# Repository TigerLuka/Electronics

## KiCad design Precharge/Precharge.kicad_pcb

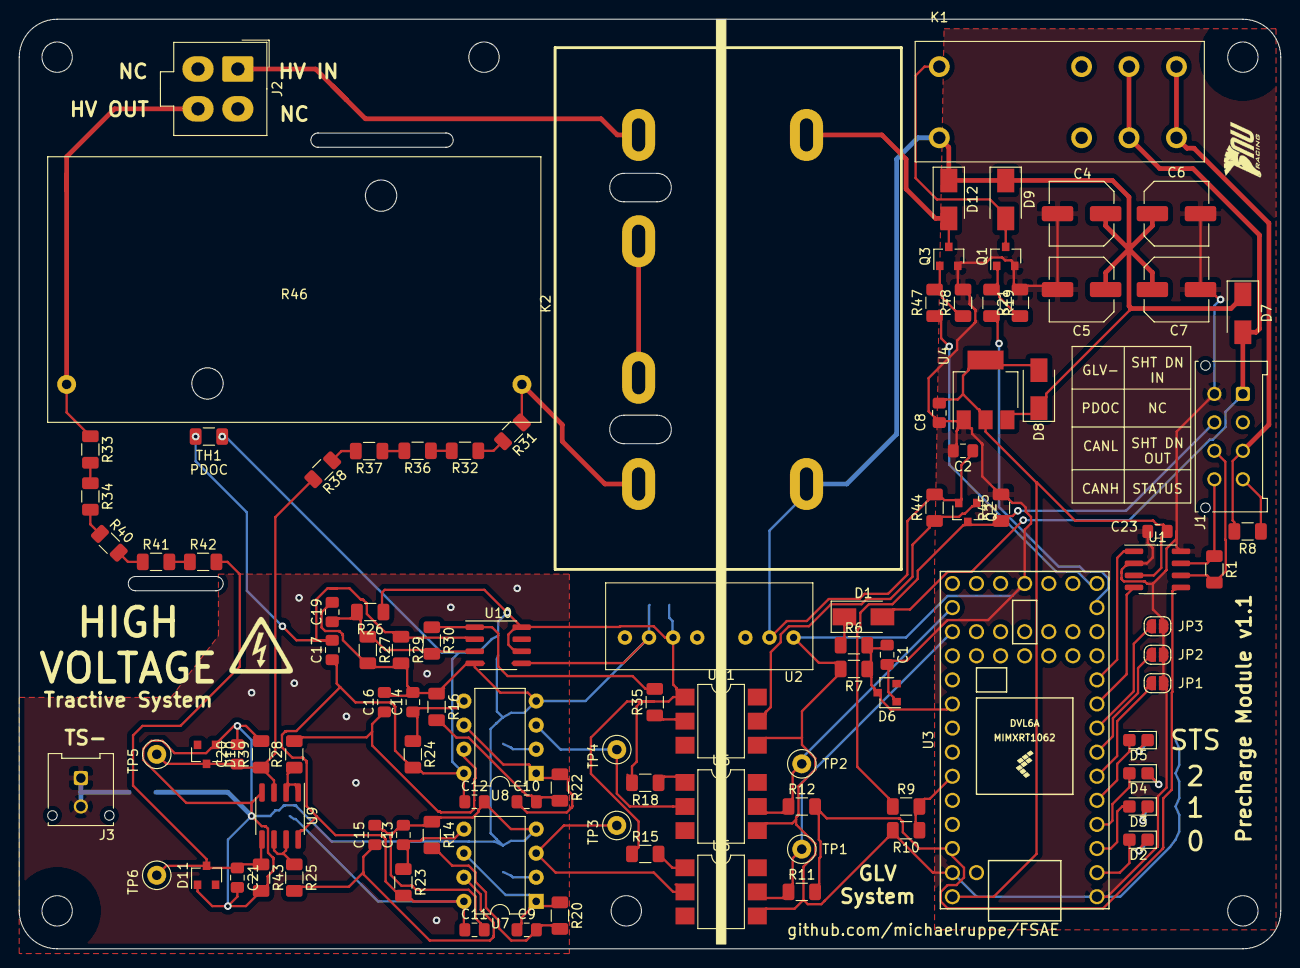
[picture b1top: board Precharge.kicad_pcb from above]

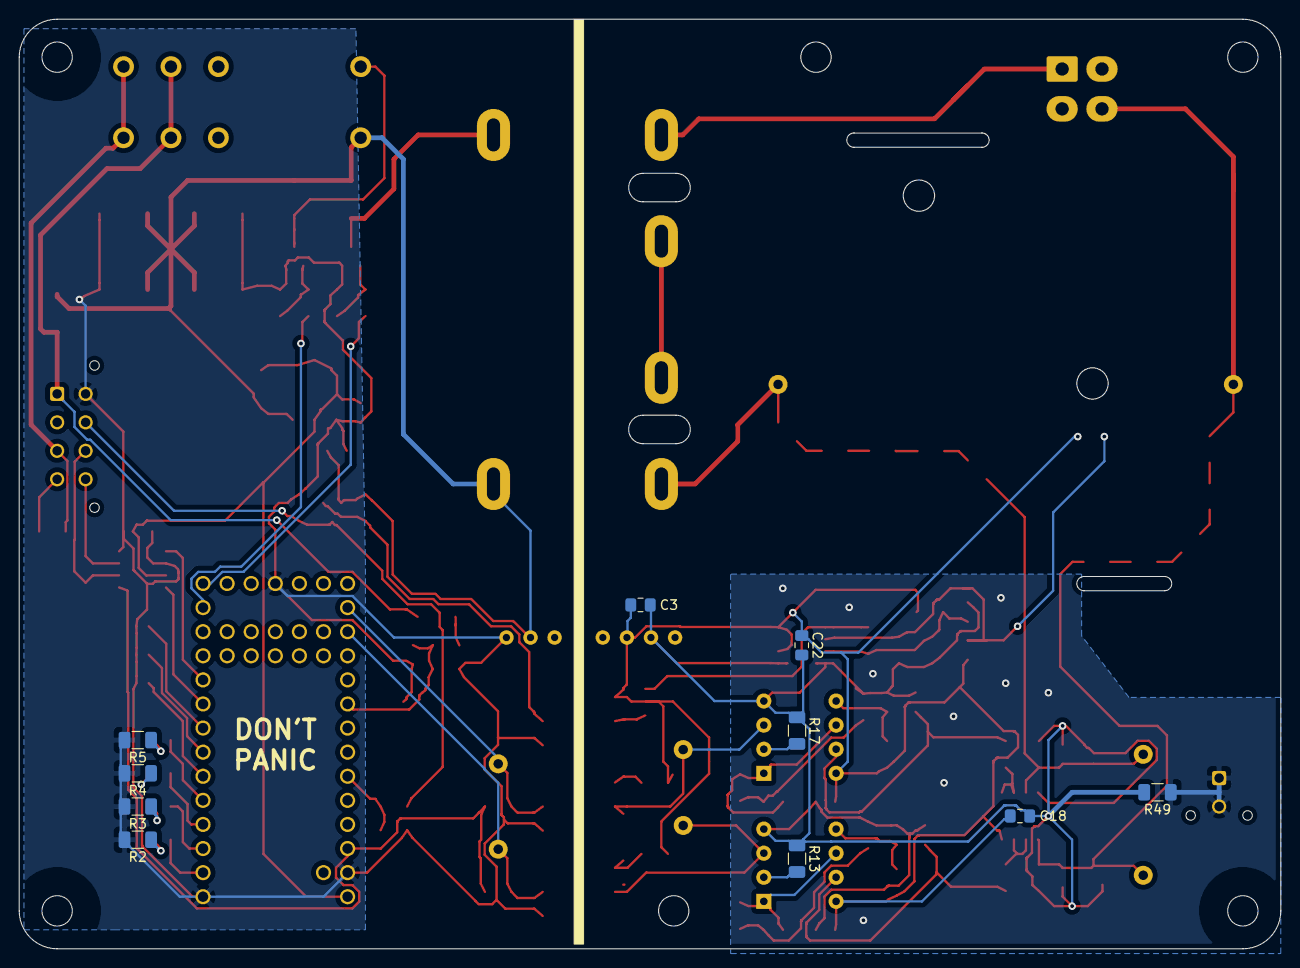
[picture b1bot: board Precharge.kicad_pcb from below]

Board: 2 copper layers, 133.0 x 98.0 mm, 119 parts (10 on the bottom side), 72 nets.

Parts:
C1, C2, C11, C12, C15, C16, C17, C18, C19, C20, C21, C22, C23: 100n; C_0805_2012Metric_Pad1.15x1.40mm_HandSolder
C3, C8, C9, C10: 1u; C_0805_2012Metric_Pad1.15x1.40mm_HandSolder
C4, C5, C6, C7: 220u; C_Elec_6.3x5.4
C13, C14: 10n; C_0805_2012Metric_Pad1.15x1.40mm_HandSolder
D1, D7, D8, D9, D12: D; D_SMA
D2, D3, D4, D5: LED; LED_0805_2012Metric_Castellated
D6: BZX84C3V3; D_SOT-23_ANK
D10, D11: BZX84C12; D_SOT-23_ANK
J1: MicroFit; Molex_Micro-Fit_3.0_43045-0812_2x04_P3.00mm_Vertical
J2: Mini-Fit_Jr_5566-04A; Molex-Mini-Fit-Jr-4-pin-P4.2mm-RowP4.2mm
J3: Micro-Fit 43045-0212; Molex_Micro-Fit_3.0_43045-0212_2x01_P3.00mm_Vertical
JP1, JP2, JP3: SolderJumper_2_Open; SolderJumper-2_P1.3mm_Open_RoundedPad1.0x1.5mm
K1: OMRON-G2RL-24; OMRON-G2R-24
K2: G7L-2A-X-L
MT1, MT2, MT3, MT4, MT5, MT6: MountingHole_3.2mm_M3
Q1, Q3: 2N7002; SOT-23
Q2: MMBT3906; SOT-23
R1: 160; R_1206_3216Metric
R2, R3, R4, R5: 200; R_1206_3216Metric
R6, R9: 20k; R_1206_3216Metric
R7, R10, R23, R24: 6k8; R_1206_3216Metric
R8, R21, R26, R27, R29, R44, R45, R48: 10k; R_1206_3216Metric
R11, R12: 1k5; R_1206_3216Metric
R13, R17: 12k; R_1206_3216Metric
R14, R16: 47; R_1206_3216Metric
R15, R18: 560; R_1206_3216Metric
R19, R47: 220; R_1206_3216Metric
R20, R22, R25, R28: 100k; R_1206_3216Metric
R30: 500k; R_1206_3216Metric
R31, R32, R33, R34, R36, R37, R38, R40, R41, R42: 510k; R_1206_3216Metric
R35: 2k2; R_1206_3216Metric
R39, R43: 39k; R_1206_3216Metric
R46: HSA25390RJ; Chassis_Resistor_TE_Connectivity_HSA25
R49: 0; R_1206_3216Metric
TH1: TFPT1206L1002FM; R_1206_3216Metric
TP1, TP2, TP3, TP4, TP5, TP6: TestPoint; TestPoint_Loop_D2.50mm_Drill1.0mm_LowProfile
U1: TJA1051T-3; SOIC-8_3.9x4.9mm_P1.27mm
U2: SPAN02A-12; SPAN02
U3: Teensy4.0; Teensy40
U4: LM1117-5.0; SOT-223-3_TabPin2
U5, U6, U11: 4N35; SMDIP-6_W7.62mm
U7, U8: LM331; DIP-8_W7.62mm
U9: LM2904; SOIC-8_3.9x4.9mm_P1.27mm
U10: LM393; SOIC-8_3.9x4.9mm_P1.27mm

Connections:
+3V3: R11.2, R12.2, U1.5, U3.31
+5V: C8.1, C23.2, D8.2, U1.3, U3.33, U4.2
+12P: C3.2, C11.1, C12.1, C17.1, C18.1, C22.1, R15.1, R18.2, R23.2, R24.2, R26.1, TH1.2, U2.6, U7.8, U8.8, U9.8, U10.6, U10.8, U11.1
+12V: C2.1, C4.1, C5.1, C6.1, C7.1, D7.1, D8.1, D9.1, D12.1, K1.8, K2.0, Q2.2, R44.2, U2.2, U4.3
/CANH: J1.8, R1.1, U1.7
/CANL: J1.7, R1.2, U1.6
/CANRX: U1.4, U3.9
/CANTX: U1.1, U3.10
/CFG0: JP1.1, U3.6
/CFG1: JP2.1, U3.7
/CFG2: JP3.1, U3.8
/Faccu: R12.1, TP2.1, U3.21, U6.5
/FoutAccu: TP4.1, U6.2, U8.3
/FoutTS: TP3.1, U5.2, U7.3
/Fts: R11.1, TP1.1, U3.22, U5.5
/PDOC_OK: J1.6, Q2.3, R9.1, R45.1
/PRECHG: R47.1, U3.14
/PRECH_STS: J1.4, R8.1
/PWR_OK: C1.1, D6.1, R6.2, R7.1, U3.25
/SHTDN_CTRL: R19.2, U3.13
/SHTDN_OUT: J1.3, K1.4, K1.5, R8.2
/TS-: J3.1, J3.2, R49.1
/VinAccu: K2.2, R31.1, R46.1
/VinTS: J2.4, R33.1, R46.2
GLV+: D1.2, D7.2, J1.1, K1.3, K1.6
GLV-: C1.2, C2.2, C4.2, C5.2, C6.2, C7.2, C8.2, C23.1, D6.2, J1.5, JP1.2, JP2.2, JP3.2, Q1.2, Q3.2, R2.2, R3.2, R4.2, R5.2, R7.2, R10.2, R21.2, R45.2, R48.2, U1.2, U1.8, U2.1, U3.1, U3.17, U3.32, U4.1, U5.4, U6.4, U11.4
GNDS: C3.1, C11.2, C12.2, C13.2, C14.2, C15.2, C16.2, C18.2, C19.2, C20.2, C21.2, C22.2, D10.2, D11.2, R13.1, R14.1, R16.1, R17.1, R27.2, R29.2, R39.2, R43.2, R49.2, U2.7, U7.4, U8.4, U9.4, U10.4, U10.5
unnamed: C9.1, R20.1, U7.1, U7.6
unnamed: C9.2, R14.2, R20.2
unnamed: C10.1, R22.1, U8.1, U8.6
unnamed: C10.2, R16.2, R22.2
unnamed: C13.1, R23.1, U7.5
unnamed: C14.1, R24.1, U8.5
unnamed: C15.1, R25.2, U7.7
unnamed: C16.1, R28.2, U8.7
unnamed: C17.2, R29.1, TH1.1, U10.2
unnamed: C19.1, R26.2, R27.1, R30.2, U10.3
unnamed: C20.1, D10.1, R38.2, R39.1, TP5.1, U9.3
unnamed: C21.1, D11.1, R42.2, R43.1, TP6.1, U9.5
unnamed: D1.1, R6.1
unnamed: D2.1, R2.1
unnamed: D2.2, U3.2
unnamed: D3.1, R3.1
unnamed: D3.2, U3.3
unnamed: D4.1, R4.1
unnamed: D4.2, U3.4
unnamed: D5.1, R5.1
unnamed: D5.2, U3.5
unnamed: D9.2, K1.1, Q1.3
unnamed: D12.2, K2.1, Q3.3
unnamed: J2.1, K2.8
unnamed: K2.4, K2.6
unnamed: Q1.1, R19.1, R21.1
unnamed: Q2.1, R44.1, U11.5
unnamed: Q3.1, R47.2, R48.1
unnamed: R9.2, R10.1, U3.28
unnamed: R13.2, U7.2
unnamed: R15.2, U5.1
unnamed: R17.2, U8.2
unnamed: R18.1, U6.1
unnamed: R25.1, U9.6, U9.7
unnamed: R28.1, U9.1, U9.2
unnamed: R30.1, R35.2, U10.1
unnamed: R31.2, R32.1
unnamed: R32.2, R36.1
unnamed: R33.2, R34.1
unnamed: R34.2, R40.1
unnamed: R35.1, U11.2
unnamed: R36.2, R37.1
unnamed: R37.2, R38.1
unnamed: R40.2, R41.1
unnamed: R41.2, R42.1

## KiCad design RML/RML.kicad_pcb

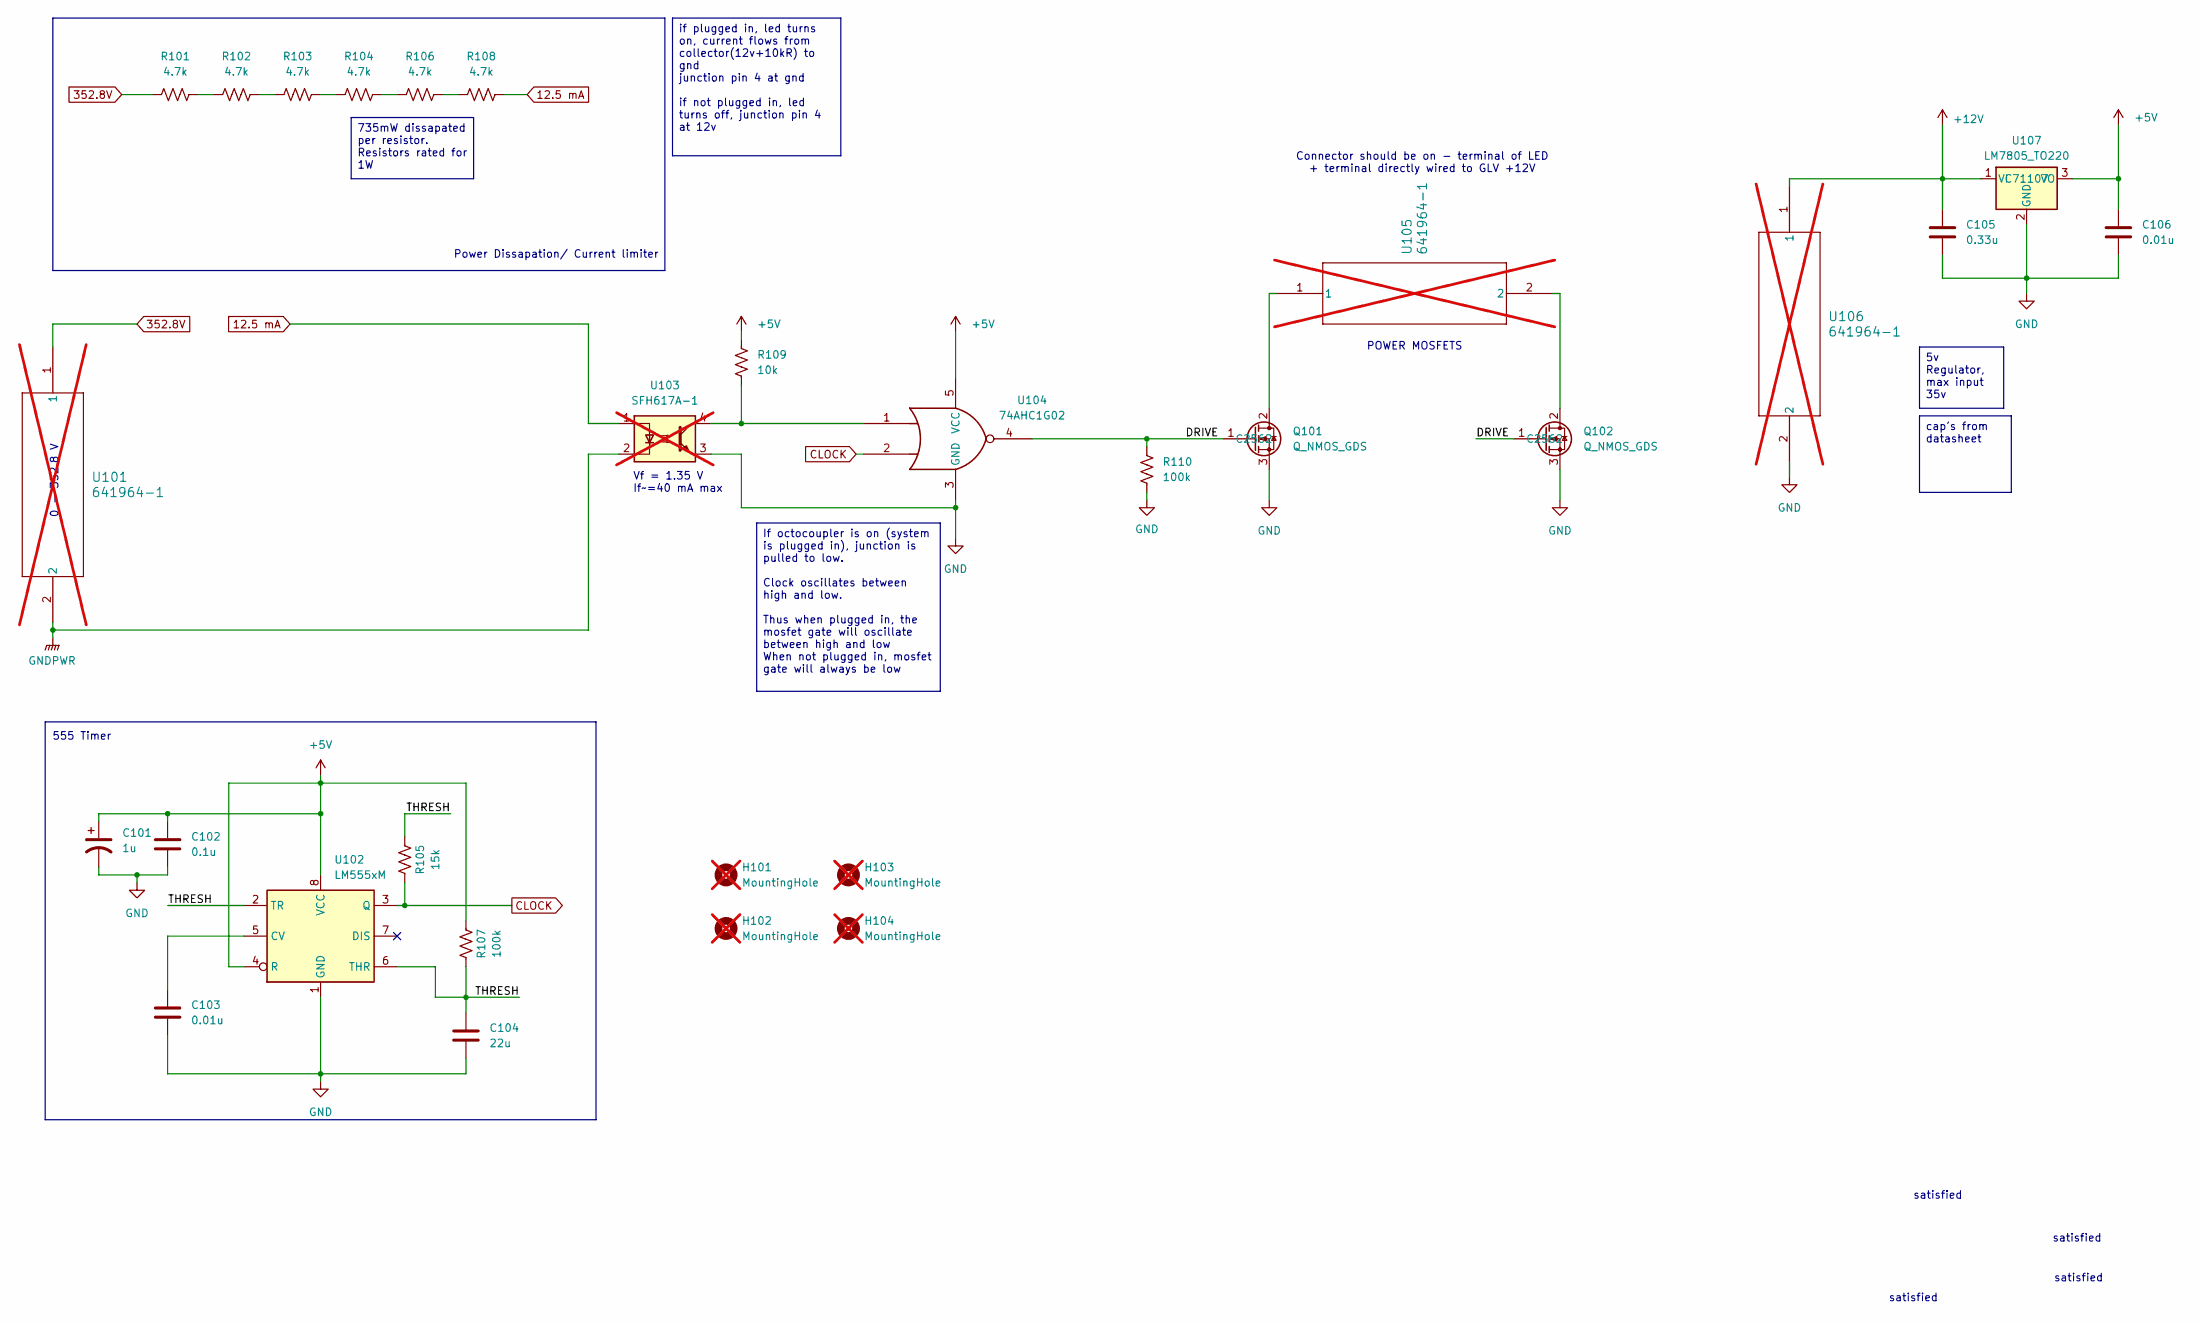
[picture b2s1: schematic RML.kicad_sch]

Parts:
C101: 1u; C_0603_1608Metric; JLC# C59782
C102: 0.1u; C_0402_1005Metric; JLC# C133086
C103, C106: 0.01u; C_0402_1005Metric; JLC# C15195
C104: 22u; C_0402_1005Metric; JLC# C105226
C105: 0.33u; C_0402_1005Metric; JLC# C107013
H101, H102, H103, H104: MountingHole; MountingHole_3.2mm_M3; not fitted
Q101, Q102: Q_NMOS_GDS; TO-220-3_Vertical; JLC# C2562
R101, R102, R103, R104, R106, R108: 4.7k; R_2512_6332Metric_Pad1.40x3.35mm_HandSolder; JLC# C163339
R105: 15k; C_0402_1005Metric; JLC# C25756
R107, R110: 100k; C_0402_1005Metric; JLC# C102750
R109: 10k; C_0402_1005Metric; JLC# C102759
U101, U105, U106: 641964-1; 641964-1_TYC; not fitted
U102: LM555xM; SOIC-8_3.9x4.9mm_P1.27mm; JLC# C90760
U103: SFH617A-1; DIP-4_W7.62mm; not fitted
U104: 74AHC1G02; SOT-23-5; JLC# C7463
U107: LM7805_TO220; TO-220-3_Vertical; JLC# C71107

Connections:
12.5 mA: R108.1, U103.1
352.8V: R101.2, U101.1
+5V: C101.1, C102.1, C106.1, R107.2, R109.1, U102.4 (R), U102.8 (VCC), U104.5 (VCC), U107.3 (VO)
+12V: C105.1, U106.1, U107.1 (VI)
/DRIVE: Q101.1 (G), Q102.1 (G), R110.2, U104.4
/THRESH: C104.2, R105.2, R107.1, U102.2 (TR), U102.6 (THR)
CLOCK: R105.1, U102.3 (Q), U104.2
GND: C101.2, C102.2, C103.2, C104.1, C105.2, C106.2, Q101.3 (S), Q102.3 (S), R110.1, U102.1 (GND), U103.3, U104.3 (GND), U106.2, U107.2 (GND)
GNDPWR: U101.2, U103.2
unnamed: Q101.2 (D), U105.1
unnamed: Q102.2 (D), U105.2
unnamed: R101.1, R102.2
unnamed: R102.1, R103.2
unnamed: R103.1, R104.2
unnamed: R104.1, R106.2
unnamed: R106.1, R108.2
unnamed: R109.2, U103.4, U104.1
unnamed: C103.1, U102.5 (CV)

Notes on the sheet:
555 Timer
POWER MOSFETS
Connector should be on - terminal of LED + terminal directly wired to GLV +12V
0 - 352.8 V
satisfied
Vf = 1.35 V If~=40 mA max
Power Dissapation/ Current limiter
if plugged in, led turns on, current flows from collector(12v+10kR) to gnd junction pin 4 at gnd if not plugged in, led turns off, junction pin 4 at 12v
cap's from datasheet
5v Regulator, max input 35v
735mW dissapated per resistor. Resistors rated for 1W
If octocoupler is on (system is plugged in), junction is pulled to low. Clock oscillates between high and low. Thus when plugged in, the mosfet gate will oscillate between high and low When not plugged in, mosfet gate will always be low

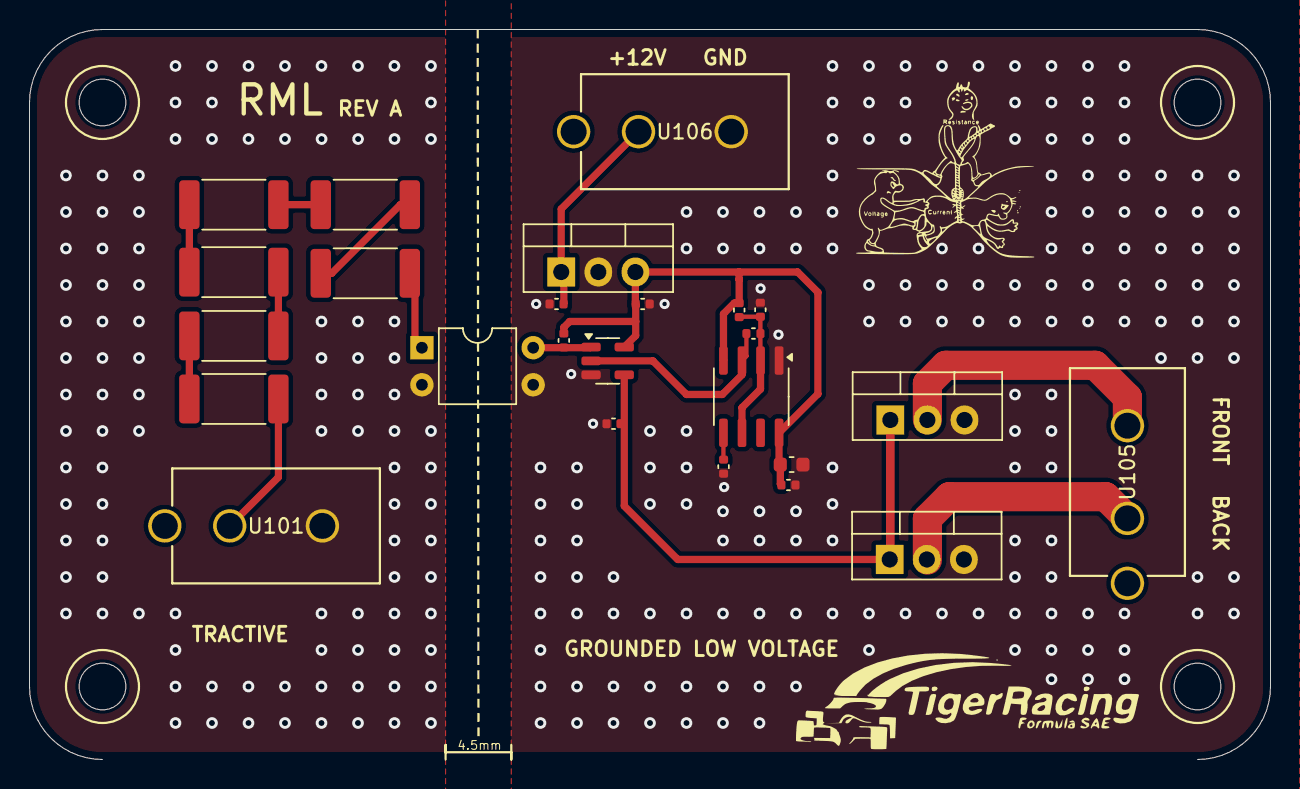
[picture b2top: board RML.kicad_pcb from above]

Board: 4 copper layers, 85.0 x 50.0 mm, 29 parts (0 on the bottom side), 18 nets.

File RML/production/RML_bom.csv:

Designator,Footprint,Quantity,Value,LCSC Part #
C101,0603,1,1u,
C102,0402,1,0.1u,
"C103, C106",0402,2,0.01u,
C104,0402,1,22u,
C105,0402,1,0.33u,
"Q101, Q102",TO-220-3_Vertical,2,Q_NMOS_GDS,
"R101, R102, R103, R104, R106, R108",2512,6,4.7k,
R105,0402,1,15k,
"R107, R110",0402,2,100k,
R109,0402,1,10k,
U102,SOIC-8_3.9x4.9mm_P1.27mm,1,LM555xM,
U104,SOT-23-5,1,74AHC1G02,
U107,TO-220-3_Vertical,1,LM7805_TO220,
